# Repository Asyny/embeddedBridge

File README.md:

# embeddedBridge

Develop and test your own embedded system without the need to build a dedicated testbench. It is as easy as following three steps:
1. Connect your device under test to the corresponding GPIOs of the embeddedBridge (see: [Features](#Features))
2. Connect the embeddedBridge to your PC
3. Send commands automatically or manually via the serial connection to the embeddedBridge and thus your device

## Features 

- 4x DOUT (2x 0 - 24 V)
- 4x AOUT (0 - 24 V)
- 4x AIN (max. 27 V)
- 1x FOUT
- 2x Relais (2x SPDT)
- 4x Level shift
- 2x RS232
- 2x CAN
- 1x Battery sim
- ESP8266 interface
- SD card
- EEPROM

## Update

- Download the .uf2 from the newest [release](https://github.com/Asyny/embeddedBridge/releases) assets
- Connect the embeddedBridge via micro USB to your PC
- Press the RESET button and the BOOTSEL simultaneously
- Let go of the RESET and afterwards the BOOTSEL button
- Move the .uf2 into the newly connected USB Drive

## Automatic vs Manual mode

The embeddedBridge will start in the automatic mode where it expects SCPI like commands. If you want to switch to the manual mode where a menu is printed on the serial interface, then you can send the command "SYStem:COMmand:INput MENU". To switch back to the automatic mode, you simple need to exit the menu.

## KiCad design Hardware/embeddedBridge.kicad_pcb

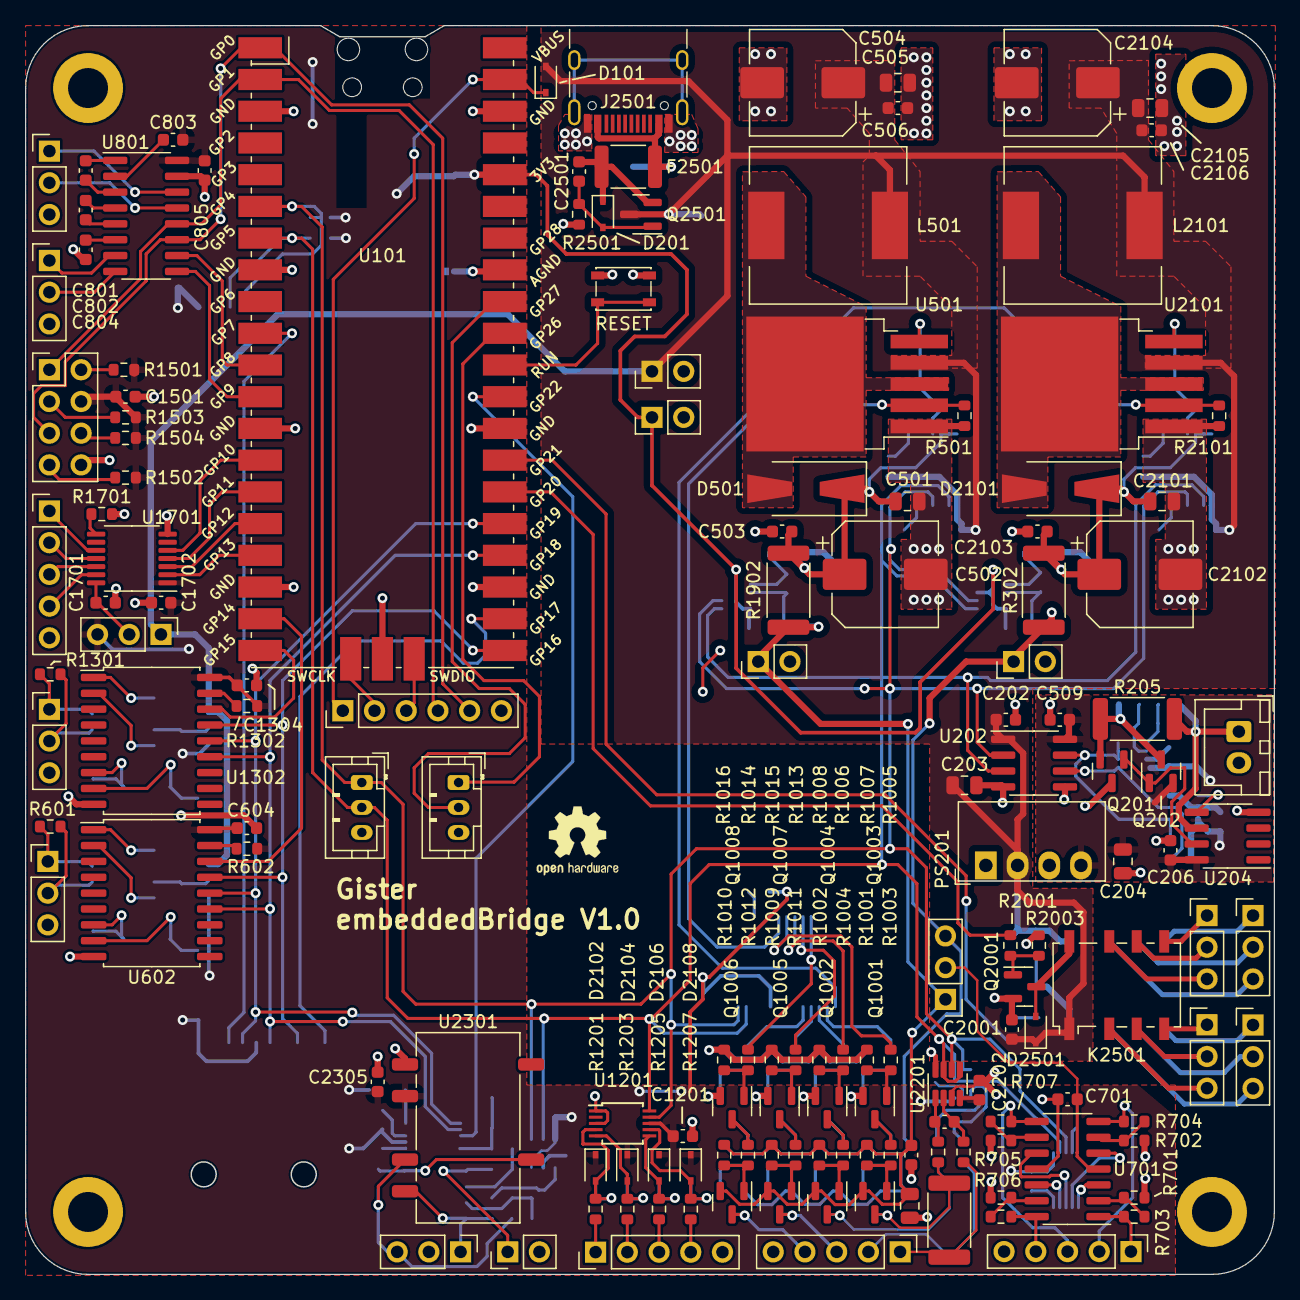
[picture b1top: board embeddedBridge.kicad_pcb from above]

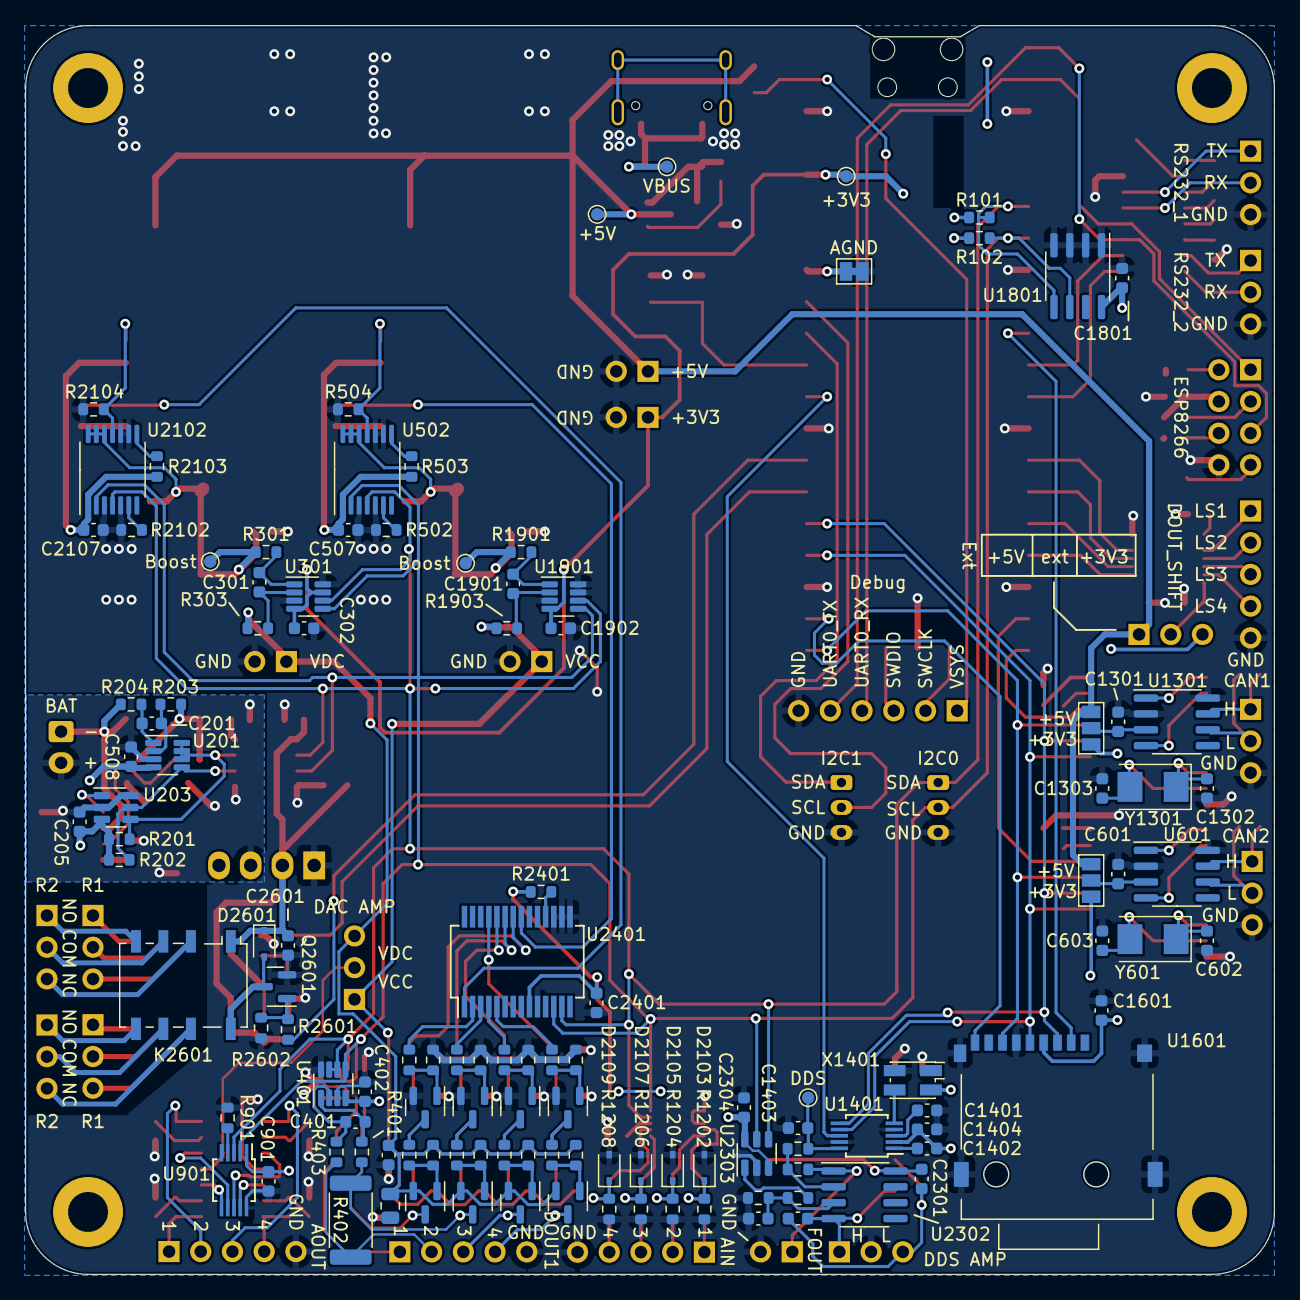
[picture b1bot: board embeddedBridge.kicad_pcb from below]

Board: 2 copper layers, 100.0 x 100.0 mm, 276 parts (122 on the bottom side), 189 nets.

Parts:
C201, C202, C205, C206, C301, C302, C401, C402, C503, C506, C507, C508, C509, C601, C604, C701, C801, C802, C803, C804, C805, C901, C1001, C1101, C1201, C1301, C1304, C1401, C1404, C1501, C1601, C1701, C1702, C1801, C1901, C1902, C2001, C2103, C2106, C2107, C2201, C2202, C2301, C2302, C2304, C2305, C2401, C2501, C2601: 100n; C_0603_1608Metric
C203, C204, C501, C505, C1002, C1102, C2101, C2105: 1u; C_0805_2012Metric
C502, C2102: 220u; CP_Elec_8x10
C504, C2104: 47u; CP_Elec_8x10
C602, C603, C1302, C1303: 22p; C_0603_1608Metric
C1402: 10n; C_0603_1608Metric
C1403: 20p; C_0603_1608Metric
C2303: 680n; C_0603_1608Metric
D101, D201, D2102, D2103, D2104, D2105, D2106, D2107, D2108, D2109, D2501, D2601: 1N5819; D_SOD-323
D501, D2101: D_Schottky; D_SMA-SMB_Universal_Handsoldering
F2501: Polyfuse; Fuse_1812_4532Metric
H101, H102, H103, H104: MountingHole_Pad; MountingHole_3.2mm_M3_DIN965_Pad
J101: AOUT; PinHeader_1x05_P2.54mm_Vertical
J102: I2C1; JST_PH_B3B-PH-K_1x03_P2.00mm_Vertical
J103: I2C0; JST_PH_B3B-PH-K_1x03_P2.00mm_Vertical
J104: Debug; PinHeader_1x06_P2.54mm_Vertical
J105: VCC; PinHeader_1x02_P2.54mm_Vertical
J106: DOUT1; PinHeader_1x05_P2.54mm_Vertical
J107: FOUT; PinHeader_1x02_P2.54mm_Vertical
J108: CAN1; PinHeader_1x03_P2.54mm_Vertical
J109: CAN2; PinHeader_1x03_P2.54mm_Vertical
J110: VDC; PinHeader_1x02_P2.54mm_Vertical
J111: R1_1; PinHeader_1x03_P2.54mm_Vertical
J112: R1_2; PinHeader_1x03_P2.54mm_Vertical
J113: R2_1; PinHeader_1x03_P2.54mm_Vertical
J114: R2_2; PinHeader_1x03_P2.54mm_Vertical
J115: RS232_2; PinHeader_1x03_P2.54mm_Vertical
J116: RS232_1; PinHeader_1x03_P2.54mm_Vertical
J117: +3V3; PinHeader_1x02_P2.54mm_Vertical
J118: +5V; PinHeader_1x02_P2.54mm_Vertical
J201: BAT; JST_XH_B2B-XH-A_1x02_P2.50mm_Vertical
J1201: AIN; PinHeader_1x05_P2.54mm_Vertical
J1501: ESP8266; PinHeader_2x04_P2.54mm_Vertical
J1701: DOUT_SHIFT; PinHeader_1x05_P2.54mm_Vertical
J2501: USB_C_Receptacle_USB2.0; USB_C_Receptacle_HRO_TYPE-C-31-M-12
JP101: AGND; SolderJumper-2_P1.3mm_Bridged_Pad1.0x1.5mm
JP601, JP1301: SolderJumper_3_Open; SolderJumper-3_P1.3mm_Open_Pad1.0x1.5mm_NumberLabels
JP701: DAC AMP; PinHeader_1x03_P2.54mm_Vertical
JP1701: Ext; PinHeader_1x03_P2.54mm_Vertical
JP2301: DDS AMP; PinHeader_1x03_P2.54mm_Vertical
K2501, K2601: G6K-2F-Y; Relay_DPDT_Omron_G6K-2F-Y
L501, L2101: 33uH; L_12x12mm_H8mm
PS201: 1S4E_0505S1U; Converter_DCDC_Murata_MEE1SxxxxSC_THT
Q201: Q_NPN_BCE; SOT-23
Q202: Q_PNP_BCE; SOT-23
Q1001, Q1002, Q1005, Q1006, Q1101, Q1102, Q1105, Q1106, Q2501: Q_PMOS_GSD; SOT-23
Q1003, Q1004, Q1007, Q1008, Q1103, Q1104, Q1107, Q1108: MMBT3904; SOT-23
Q2001, Q2601: Q_NMOS_GSD; SOT-23
R101, R102, R201, R202, R901, R2301: 4k7; R_0603_1608Metric
R203, R204, R301, R303, R401, R403, R1901, R1903, R2201, R2203: 10R; R_0603_1608Metric
R205, R302, R402, R1902, R2202: 100R; R_2512_6332Metric
R501, R502, R503, R602, R701, R702, R705, R706, R1001, R1002, R1005, R1006, R1009, R1010, R1013, R1014, R1101, R1102, R1105, R1106, R1109, R1110, R1113, R1114, R1302, R1501, R1502, R1503, R1504, R1701, R2001, R2101, R2102, R2103, R2304, R2401, R2601: 10k; R_0603_1608Metric
R504, R2104: 470R; R_0603_1608Metric
R601, R1301: 120R; R_0603_1608Metric
R703, R704, R707, R708: 68k; R_0603_1608Metric
R1003, R1004, R1007, R1008, R1011, R1012, R1015, R1016, R1103, R1104, R1107, R1108, R1111, R1112, R1115, R1116, R2003, R2501, R2602: 100k; R_0603_1608Metric
R1201, R1203, R1205, R1207: 12k; R_0603_1608Metric
R1202, R1204, R1206, R1208: 1k5; R_0603_1608Metric
R2302: 39k; R_0603_1608Metric
R2303: 1k; R_0603_1608Metric
SW101: RESET; SW_SPST_PTS810
TP101: +3V3; TestPoint_Pad_D1.0mm
TP102: DDS; TestPoint_Pad_D1.0mm
TP201: VBUS; TestPoint_Pad_D1.0mm
TP202: +5V; TestPoint_Pad_D1.0mm
TP501, TP2101: Boost; TestPoint_Pad_D1.0mm
U101: Pico; RPi_Pico_SMD_TH
U201, U301, U401, U1901, U2201: INA219AxDCN; SOT-23-8
U202: ISO1540; SOIC-8_3.9x4.9mm_P1.27mm
U203, U2303: MCP4725xxx-xCH; SOT-23-6
U204, U2302: Opamp_Dual; SOIC-8_3.9x4.9mm_P1.27mm
U501, U2101: XL6009; TO-263-5_TabPin3
U502, U2102: MCP45HV31-ST; TSSOP-14_4.4x5mm_P0.65mm
U601, U1301: TJA1051T-3; SOIC-8_3.9x4.9mm_P1.27mm
U602, U1302: MCP2515-xSO; SOIC-18W_7.5x11.6mm_P1.27mm
U701: LM324; SOIC-14_3.9x8.7mm_P1.27mm
U801: MAX3232; SOIC-16_3.9x9.9mm_P1.27mm
U901: MCP4728; MSOP-10_3x3mm_P0.5mm
U1201: ADS1115IDGS; TSSOP-10_3x3mm_P0.5mm
U1401: AD9833xRM; MSOP-10_3x3mm_P0.5mm
U1601: TF-01A; FT-01A
U1701: TXB0104PW; TSSOP-14_4.4x5mm_P0.65mm
U1801: 24LC32; SOIC-8_3.9x4.9mm_P1.27mm
U2301: PDS1-M; PSD1
U2401: MCP23017_SS; SSOP-28_5.3x10.2mm_P0.65mm
X1401: XO32; Oscillator_SMD_EuroQuartz_XO32-4Pin_3.2x2.5mm_HandSoldering
Y601, Y1301: 8MHz; Crystal_SMD_5032-2Pin_5.0x3.2mm

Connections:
+3V3: C302.1, C402.1, C604.1, C803.1, C805.1, C901.1, C1201.1, C1304.1, C1402.1, C1404.1, C1501.1, C1601.1, C1702.1, C1801.1, C1902.1, C2202.1, C2304.1, C2305.1, C2401.1, D2102.1 (K), D2104.1 (K), D2106.1 (K), D2108.1 (K), J117.1, J1501.4, JP601.1 (A), JP1301.1 (A), JP1701.3 (B), R101.2, R102.2, R602.1, R1302.1, R1501.1, R1502.1, R1503.2, R1504.2, R2401.1, TP101.1, U101.36 (3V3), U301.4 (VS), U301.7 (A0), U401.4 (VS), U602.18 (VDD), U801.16 (VCC), U901.1 (VDD), U1201.8 (VDD), U1302.18 (VDD), U1401.2 (VDD), U1601.4 (VDD), U1701.1 (VCCA), U1801.8 (VCC), U1901.4 (VS), U2201.4 (VS), U2301.2 (Vin), U2303.3 (VDD), U2303.6 (A0), U2401.9 (VDD), X1401.4 (V+)
+5V: C202.1, C203.1, C504.1, C505.1, C506.1, C507.1, C2001.1, C2104.1, C2105.1, C2106.1, C2107.1, C2601.1, D101.2 (A), D2501.1 (K), D2601.1 (K), J118.1, JP601.3 (B), JP1301.3 (B), JP1701.1 (A), K2501.1, K2601.1, L501.1, L2101.1, PS201.2 (+Vin), Q2501.3 (D), R503.2, R2103.2, TP202.1, U202.1 (VCC1), U501.4 (VIN), U502.1 (VL), U2101.4 (VIN), U2102.1 (VL)
+5VD: C204.1, C205.1, C206.1, C508.1, C509.1, PS201.4 (+Vout), Q201.2 (C), R201.1, R202.1, U201.4 (VS), U202.8 (VCC2), U203.3 (VDD), U204.8 (V+)
/AMP1/IN1+: U701.3 (+), U901.6 (VOUTA)
/AMP1/IN2+: U701.5 (+), U901.7 (VOUTB)
/AMP1/IN3+: U701.10 (+), U901.8 (VOUTC)
/AMP1/IN4+: U701.12 (+), U901.9 (VOUTD)
/AMP1/OUT1: J101.1, R703.2, U701.1
/AMP1/OUT2: J101.2, R704.2, U701.7
/AMP1/OUT3: J101.3, R707.2, U701.8
/AMP1/OUT4: J101.4, R708.2, U701.14
/AMP_offset/IN: C1403.1, R2301.2, TP102.1, U1401.10 (VOUT)
/AMP_offset/OUT: J107.1, R2302.2, U2302.1
/Battery/BAT+: J201.1, R204.1, R205.2, U204.6 (-)
/Battery/BAT+_: Q201.3 (E), Q202.2 (C), R203.1, R205.1
/Battery/SCL_: R202.2, U201.5 (SCL), U202.6 (SCL2), U203.5 (SCL)
/Battery/SDA_: R201.2, U201.6 (SDA), U201.7 (A0), U201.8 (A1), U202.7 (SDA2), U203.4 (SDA)
/CAN1/CANH: J108.1, R1301.2, U1301.7 (CANH)
/CAN1/CANL: J108.2, R1301.1, U1301.6 (CANL)
/CAN2/CANH: J109.1, R601.2, U601.7 (CANH)
/CAN2/CANL: J109.2, R601.1, U601.6 (CANL)
/CD_SD: U101.22 (GPIO17), U1601.9 (CD)
/Cu1+: C501.1, C502.1, C503.1, D501.1 (K), R1901.1, R1902.1, TP501.1, U502.12 (P0W), U502.13 (P0A), U502.14 (V+)
/Cu2+: C2101.1, C2102.1, C2103.1, D2101.1 (K), R301.1, R302.1, TP2101.1, U2102.12 (P0W), U2102.13 (P0A), U2102.14 (V+)
/Cu3+: Q1002.3 (D), Q1102.3 (D), R401.1, R402.1
/Cu3-: J106.2, R402.2, R403.1
/Cu4+: Q1001.3 (D), Q1101.3 (D), R2201.1, R2202.1
/Cu4-: J106.1, R2202.2, R2203.1
/DAC1/LDAC: R901.1, U901.4 (~LDAC)
/DOUT1_LS: U101.14 (GPIO10), U1701.5 (A4)
/DOUT2_LS: U101.15 (GPIO11), U1701.4 (A3)
/DOUT3_LS: U101.16 (GPIO12), U1701.3 (A2)
/DOUT4_LS: U101.17 (GPIO13), U1701.2 (A1)
/ESP8266/EN: J1501.2, R1501.2
/ESP8266/IO0: J1501.6, R1504.1
/ESP8266/IO2: J1501.7, R1502.2
/ESP8266/RST: J1501.3, R1503.1
/I2C0_SCL: J103.2, R102.1, U101.7 (GPIO5), U202.3 (SCL1), U301.5 (SCL), U401.5 (SCL), U502.2 (SCL), U901.2 (SCL), U1201.10 (SCL), U1801.6 (SCL), U1901.5 (SCL), U2102.2 (SCL), U2201.5 (SCL), U2201.7 (A0), U2303.5 (SCL), U2401.12 (SCK)
/I2C0_SDA: J103.1, R101.1, U101.6 (GPIO4), U202.2 (SDA1), U301.6 (SDA), U401.6 (SDA), U401.7 (A0), U502.4 (SDA), U901.3 (SDA), U1201.9 (SDA), U1801.5 (SDA), U1901.6 (SDA), U2102.4 (SDA), U2201.6 (SDA), U2303.4 (SDA), U2401.13 (SDA)
/I2C1_SCL: J102.2, U101.32 (GPIO27_ADC1)
/I2C1_SDA: J102.1, U101.31 (GPIO26_ADC0)
/IO_Expander/GPA1: R1005.1, U2401.22 (GPA1)
/IO_Expander/GPA2: R1006.1, U2401.23 (GPA2)
/IO_Expander/GPA3: R1013.1, U2401.24 (GPA3)
/IO_Expander/GPA4: R1014.1, U2401.25 (GPA4)
/IO_Expander/GPB1: R1105.1, U2401.2 (GPB1)
/IO_Expander/GPB2: R1106.1, U2401.3 (GPB2)
/IO_Expander/GPB3: R1113.1, U2401.4 (GPB3)
/IO_Expander/GPB4: R1114.1, U2401.5 (GPB4)
/Level Shift/OE: R1701.1, U1701.8 (OE)
/Power1/FB: R504.1, U501.5 (FB), U502.11 (P0B)
/Power1/SW: D501.2 (A), L501.2, U501.3 (SW)
/Power2/FB: R2104.1, U2101.5 (FB), U2102.11 (P0B)
/Power2/SW: D2101.2 (A), L2101.2, U2101.3 (SW)
/RUN: SW101.1 (A), U101.30 (RUN)
/Relais1: R2001.1, U101.26 (GPIO20)
/Relais1/COM1: J111.2, K2501.3
/Relais1/COM2: J112.2, K2501.6
/Relais1/NC1: J111.3, K2501.2
/Relais1/NC2: J112.3, K2501.7
/Relais1/NO1: J111.1, K2501.4
/Relais1/NO2: J112.1, K2501.5
/Relais2: R2601.1, U101.27 (GPIO21)
/Relais2/COM1: J113.2, K2601.3
/Relais2/COM2: J114.2, K2601.6
/Relais2/NC1: J113.3, K2601.2
/Relais2/NC2: J114.3, K2601.7
/Relais2/NO1: J113.1, K2601.4
/Relais2/NO2: J114.1, K2601.5
/SPI0_CS_CAN1: U101.20 (GPIO15), U1302.16 (~CS)
/SPI0_CS_CAN2: U101.19 (GPIO14), U602.16 (~CS)
/SPI0_CS_DDS: U101.29 (GPIO22), U1401.8 (~FSYNC)
/SPI0_CS_SD: U101.10 (GPIO7), U1601.2 (CDDAT3(CS))
/SPI0_MISO: U101.21 (GPIO16), U602.15 (SO), U1302.15 (SO), U1601.7 (DAT0(D0))
/SPI0_MOSI: U101.25 (GPIO19), U602.14 (SI), U1302.14 (SI), U1401.6 (SDATA), U1601.3 (CMD(DI))
/SPI0_SCK: U101.24 (GPIO18), U602.13 (SCK), U1302.13 (SCK), U1401.7 (SCLK), U1601.5 (CLK(SCLK))
/SWCLK: J104.2, U101.41 (SWCLK)
/SWDIO: J104.3, U101.43 (SWDIO)
/Switch1/DOUT3: J106.3, Q1005.3 (D), Q1105.3 (D)
/Switch1/DOUT4: J106.4, Q1006.3 (D), Q1106.3 (D)
/UART0_RX: J104.4, J1501.1, U101.2 (GPIO1), U801.12 (R1OUT)
/UART0_TX: J104.5, J1501.5, U101.1 (GPIO0), U801.11 (T1IN)
/UART1_RX: U101.12 (GPIO9), U801.9 (R2OUT)
/UART1_TX: U101.11 (GPIO8), U801.10 (T2IN)
/UART to RS232/RX1: J116.2, U801.13 (R1IN)
/UART to RS232/RX2: J115.2, U801.8 (R2IN)
/UART to RS232/TX1: J116.1, U801.14 (T1OUT)
/UART to RS232/TX2: J115.1, U801.7 (T2OUT)
/USB/VBUS: F2501.1, J2501.A4 (VBUS), J2501.A9 (VBUS), J2501.B4 (VBUS), J2501.B9 (VBUS), TP201.1
/USB/VBUS_FUSED: C2501.1, D201.1 (K), F2501.2, Q2501.2 (S)
/VCC_EN: R501.1, U501.2 (EN), U2401.21 (GPA0)
/VDC_EN: R2101.1, U2101.2 (EN), U2401.1 (GPB0)
/VSYS: D101.1 (K), J104.1, U101.39 (VSYS)
GND: C202.2, C203.2, C302.2, C402.2, C501.2, C502.2, C503.2, C504.2, C505.2, C506.2, C507.2, C601.2, C602.2, C603.2, C604.2, C701.2, C804.1, C805.2, C901.2, C1001.2, C1002.2, C1101.2, C1102.2, C1201.2, C1301.2, C1302.2, C1303.2, C1304.2, C1401.2, C1403.2, C1404.2, C1501.2, C1601.2, C1701.2, C1702.2, C1801.2, C1902.2, C2001.2, C2101.2, C2102.2, C2103.2, C2104.2, C2105.2, C2106.2, C2107.2, C2202.2, C2303.2, C2304.2, C2305.2, C2401.2, C2601.2, D2103.2 (A), D2105.2 (A), D2107.2 (A), D2109.2 (A), J101.5, J102.3, J103.3, J104.6, J105.2, J106.5, J107.2, J108.3, J109.3, J110.2, J115.3, J116.3, J117.2, J118.2, J1201.5, J1501.8, J1701.5, J2501.A1 (GND), J2501.A12 (GND), J2501.B1 (GND), J2501.B12 (GND), JP101.1 (A), JP2301.2 (C), PS201.1 (-Vin), Q1003.2 (E), Q1004.2 (E), Q1007.2 (E), Q1008.2 (E), Q1103.2 (E), Q1104.2 (E), Q1107.2 (E), Q1108.2 (E), Q2001.2 (S), Q2601.2 (S), R501.2, R502.2, R504.2, R701.1, R702.1, R705.1, R706.1, R901.2, R1007.2, R1008.2, R1015.2, R1016.2, R1107.2, R1108.2, R1115.2, R1116.2, R1202.2, R1204.2, R1206.2, R1208.2, R1701.2, R2003.2, R2101.2, R2102.2, R2104.2, R2304.2, R2501.2, R2602.2, SW101.2 (B), U101.3 (GND), U101.8 (GND), U101.13 (GND), U101.18 (GND), U101.23 (GND), U101.28 (GND), U101.38 (GND), U101.42 (GND), U202.4 (GND1), U301.3 (GND), U301.8 (A1), U401.3 (GND), U401.8 (A1), U501.1 (GND), U502.3 (A1), U502.5 (A0), U502.9 (DGND), U502.10 (V-), U601.2 (GND), U601.8 (S), U602.9 (VSS), U701.11 (V-), U801.15 (GND), U901.10 (VSS), U1201.1 (ADDR), U1201.3 (GND), U1301.2 (GND), U1301.8 (S), U1302.9 (VSS), U1401.4 (DGND), U1401.9 (AGND), U1601.6 (VSS), U1601.10 (GND), U1601.11 (GND), U1601.12 (GND), U1601.13 (GND), U1701.7 (GND), U1801.1 (A0), U1801.2 (A1), U1801.3 (A2), U1801.4 (GND), U1901.3 (GND), U1901.7 (A0), U1901.8 (A1), U2101.1 (GND), U2102.3 (A1), U2102.5 (A0), U2102.9 (DGND), U2102.10 (V-), U2201.3 (GND), U2201.8 (A1), U2301.1 (GND), U2303.2 (VSS), U2401.10 (VSS), U2401.15 (A0), U2401.16 (A1), U2401.17 (A2), X1401.2 (GND)
GNDA: JP101.2 (B), U101.33 (AGND)
GNDD: C204.2, C205.2, C206.2, C508.2, C509.2, J201.2, PS201.3 (-Vout), Q202.3 (E), U201.3 (GND), U202.5 (GND2), U203.2 (VSS), U203.6 (A0), U204.4 (V-)
unnamed: C201.1, R203.2, U201.2 (IN-)
unnamed: C201.2, R204.2, U201.1 (IN+)
unnamed: C301.1, R301.2, U301.1 (IN+)
unnamed: C301.2, R303.2, U301.2 (IN-)
unnamed: C401.1, R401.2, U401.1 (IN+)
unnamed: C401.2, R403.2, U401.2 (IN-)
unnamed: C601.1, JP601.2 (C), U601.3 (VCC)
unnamed: C602.1, U602.7 (OSC2), Y601.1
unnamed: C603.1, U602.8 (OSC1), Y601.2
unnamed: C701.1, JP701.2 (C), U701.4 (V+)
unnamed: C801.1, U801.3 (C1-)
unnamed: C801.2, U801.1 (C1+)
unnamed: C802.1, U801.5 (C2-)
unnamed: C802.2, U801.4 (C2+)
unnamed: C803.2, U801.2 (VS+)
unnamed: C804.2, U801.6 (VS-)
unnamed: C1301.1, JP1301.2 (C), U1301.3 (VCC)
unnamed: C1302.1, U1302.7 (OSC2), Y1301.1
unnamed: C1303.1, U1302.8 (OSC1), Y1301.2
unnamed: C1401.1, U1401.3 (CAP/2.5V)
unnamed: C1402.2, U1401.1 (COMP)
unnamed: C1701.1, JP1701.2 (C), U1701.14 (VCCB)
unnamed: C1901.1, R1901.2, U1901.1 (IN+)
unnamed: C1901.2, R1903.2, U1901.2 (IN-)
unnamed: C2201.1, R2201.2, U2201.1 (IN+)
unnamed: C2201.2, R2203.2, U2201.2 (IN-)
unnamed: C2301.1, U2301.7 (+Vo), U2302.8 (V+)
unnamed: C2301.2, C2302.1, JP2301.3 (B), U2301.4 (0V)
unnamed: C2302.2, JP2301.1 (A), U2301.5 (-Vo), U2302.4 (V-)
unnamed: C2303.1, R2303.1, R2304.1, U2302.3 (+)
unnamed: C2501.2, D201.2 (A), Q2501.1 (G), R2501.1
unnamed: D2102.2 (A), D2103.1 (K), R1201.2, R1202.1, U1201.4 (AIN0)
unnamed: D2104.2 (A), D2105.1 (K), R1203.2, R1204.1, U1201.5 (AIN1)
unnamed: D2106.2 (A), D2107.1 (K), R1205.2, R1206.1, U1201.6 (AIN2)
unnamed: D2108.2 (A), D2109.1 (K), R1207.2, R1208.1, U1201.7 (AIN3)
unnamed: D2501.2 (A), K2501.8, Q2001.3 (D)
unnamed: D2601.2 (A), K2601.8, Q2601.3 (D)
unnamed: J1201.1, R1201.1
unnamed: J1201.2, R1203.1
unnamed: J1201.3, R1205.1
unnamed: J1201.4, R1207.1
unnamed: J1701.1, U1701.10 (B4)
unnamed: J1701.2, U1701.11 (B3)
unnamed: J1701.3, U1701.12 (B2)
unnamed: J1701.4, U1701.13 (B1)
unnamed: Q201.1 (B), Q202.1 (B), U204.7
unnamed: Q1001.1 (G), R1001.2, R1003.1
unnamed: Q1002.1 (G), R1002.2, R1004.1
unnamed: Q1003.1 (B), R1005.2, R1007.1
unnamed: Q1003.3 (C), R1003.2
unnamed: Q1004.1 (B), R1006.2, R1008.1
unnamed: Q1004.3 (C), R1004.2
unnamed: Q1005.1 (G), R1009.2, R1011.1
unnamed: Q1006.1 (G), R1010.2, R1012.1
unnamed: Q1007.1 (B), R1013.2, R1015.1
unnamed: Q1007.3 (C), R1011.2
unnamed: Q1008.1 (B), R1014.2, R1016.1
unnamed: Q1008.3 (C), R1012.2
unnamed: Q1101.1 (G), R1101.2, R1103.1
unnamed: Q1102.1 (G), R1102.2, R1104.1
unnamed: Q1103.1 (B), R1105.2, R1107.1
unnamed: Q1103.3 (C), R1103.2
unnamed: Q1104.1 (B), R1106.2, R1108.1
unnamed: Q1104.3 (C), R1104.2
unnamed: Q1105.1 (G), R1109.2, R1111.1
unnamed: Q1106.1 (G), R1110.2, R1112.1
unnamed: Q1107.1 (B), R1113.2, R1115.1
unnamed: Q1107.3 (C), R1111.2
unnamed: Q1108.1 (B), R1114.2, R1116.1
unnamed: Q1108.3 (C), R1112.2
unnamed: Q2001.1 (G), R2001.2, R2003.1
unnamed: Q2601.1 (G), R2601.2, R2602.1
unnamed: R502.1, U502.6 (~WLAT)
unnamed: R503.1, U502.8 (~SHDN)
unnamed: R602.2, U602.17 (~RESET)
unnamed: R701.2, R703.1, U701.2 (-)
unnamed: R702.2, R704.1, U701.6 (-)
unnamed: R705.2, R707.1, U701.9 (-)
unnamed: R706.2, R708.1, U701.13 (-)
unnamed: R1302.2, U1302.17 (~RESET)
unnamed: R2102.1, U2102.6 (~WLAT)
unnamed: R2103.1, U2102.8 (~SHDN)
unnamed: R2301.1, R2302.1, U2302.2 (-)
unnamed: R2303.2, U2303.1 (VOUT)
unnamed: R2401.2, U2401.18 (~RESET)
unnamed: U203.1 (VOUT), U204.5 (+)
unnamed: U601.1 (TXD), U602.1 (TXCAN)
unnamed: U601.4 (RXD), U602.2 (RXCAN)
unnamed: U1301.1 (TXD), U1302.1 (TXCAN)
unnamed: U1301.4 (RXD), U1302.2 (RXCAN)
unnamed: U1401.5 (MCLK), X1401.3 (OUT)
VCC: C1001.1, C1002.1, J105.1, JP701.1 (A), Q1001.2 (S), Q1002.2 (S), Q1005.2 (S), Q1006.2 (S), R1001.1, R1002.1, R1009.1, R1010.1, R1902.2, R1903.1
VDC: C1101.1, C1102.1, J110.1, JP701.3 (B), Q1101.2 (S), Q1102.2 (S), Q1105.2 (S), Q1106.2 (S), R302.2, R303.1, R1101.1, R1102.1, R1109.1, R1110.1

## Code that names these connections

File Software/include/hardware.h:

#ifndef HARDWARE_H
#define HARDWARE_H

// third party libraries
#include <Arduino.h>
#include <Arduino_DebugUtils.h>

#define DEBUG_SERIAL Serial1
#define DEBUG_LEVEL DBG_WARNING	// DBG_NONE, DBG_ERROR, DBG_WARNING, DBG_INFO, DBG_DEBUG, DBG_VERBOSE

// datasheets
//MCP45HV31 https://eu.mouser.com/datasheet/2/268/20005304A-347268.pdf

// Serial
#define SERIAL_BAUD 115200
// UART
#define UART0_BAUD 115200
#define UART0_TX 0
#define UART0_RX 1
#define UART1_BAUD 115200
#define UART1_TX 8
#define UART1_RX 9

// SPI
#define SPI0_SCK 18
#define SPI0_MOSI 19
#define SPI0_MISO 16
// SPI CS
#define AD9833_DDS_CS 22
#define MCP2515_CAN1_CS 15
#define MCP2515_CAN2_CS 14
#define SD_CS 7

// GPIOs
#define LED_PIN 25
#define RELAIS1_PIN 20
#define RELAIS2_PIN 21
#define LEVELSHIFT1_PIN 10
#define LEVELSHIFT2_PIN 11
#define LEVELSHIFT3_PIN 12
#define LEVELSHIFT4_PIN 13
#define AMP_HL 3
#define SD_CD 17

// I2C
#define I2C0_SDA 4
#define I2C0_SCL 5
#define I2C1_SDA 26
#define I2C1_SCL 27
// I2C Adresses
#define INA219_VCC_ADDR 0x40
#define INA219_VDC_ADDR 0x41
#define INA219_DOUT1_ADDR 0x42
#define INA219_DOUT2_ADDR 0x43
#define INA219_BAT_ADDR 0x4A
#define MCP23017_DOUT_ADDR 0x20	
//#define MCP4728_AOUT_ADDR 0x60	// ToDo: BUG same adress as MCP4725 Battery
#define MCP4725_BAT_ADDR 0x60 // AJxx=110000n, APxx=110001n, AQxx=110010n, ARxx=110011n
#define MCP4725_DDSOFFSET_ADDR 0x61
#define ADS1115_AIN_ADDR 0x48
#define EEPROM_ADDR 0x50
#define MCP45HV31_VCC_ADDR 0x3C
#define MCP45HV31_VDC_ADDR 0x3D	// ToDo: BUG same address as MCP45HV31_VCC_ADDR

// MCP23017 GPIOs
#define VCC_EN_PIN 0
#define VCC_DOUT1_PIN 1
#define VCC_DOUT2_PIN 2
#define VCC_DOUT3_PIN 3
#define VCC_DOUT4_PIN 4
//#define UNUSED 5
//#define UNUSED 6
//#define UNUSED 7
#define VDC_EN_PIN 8
#define VDC_DOUT1_PIN 9
#define VDC_DOUT2_PIN 10
#define VDC_DOUT3_PIN 11
#define VDC_DOUT4_PIN 12
//#define UNUSED 13
//#define UNUSED 14
//#define UNUSED 15

// Settings
#define VCC_VDC_MAX_VOLTAGE 27.0

#define MCP23017_MAX_PIN 15

#define AIN1_VOLTAGE_DEVIDER 9.1266
#define AIN2_VOLTAGE_DEVIDER 9.1266
#define AIN3_VOLTAGE_DEVIDER 9.1266
#define AIN4_VOLTAGE_DEVIDER 9.1266

#define FOUT_OFFSET_MULTIPLIER 160
#define BAT_MULTIPLIER 790
#define VCC_VOLTAGE_MULTIPLIER 4.561 // 1.25*(1+100k/4k7)=27.846V; max wiper (100k) = 127 -> 27.846 = 127, 0.219 = 1
#define VDC_VOLTAGE_MULTIPLIER 4.561

#define MENU_SERIAL Serial

#endif // HARDWARE_H

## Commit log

2022-07-14 layout
2022-07-14 added readme
2022-08-29 add software
2022-12-05 introduce HAL
2022-12-06 move serial menu to separate file (partly working)
2022-12-07 move serial menu to separate file (working)
2022-12-12 set USB port as menu serial; fix AIN2_VOLTAGE_DEVIDER values
2022-12-12 introduce data model for setting and getting hardware (global variables with namespace)
2022-12-12 move all menu serial variables into global scope
2022-12-12 set debug build option as default
2022-12-12 move functions for reading hardware into separate class
2022-12-12 add support for reading INA219 values
2022-12-19 remove Vrekrer SCPI parser library
2022-12-19 switch to debug serial interface
2022-12-19 add support to switch between SCPI and MENU SERIAL interface for sending commands
2022-12-19 add buffered reading from serial interface
2022-12-19 introduce debug level
2022-12-19 centralize HAL access via DataHandling component, remove HAL dependency from CommandHandling
2022-12-19 fix compiler warnings
2022-12-20 set initial ADC gain to 1 instead of auto (auto is not supported)
2022-12-20 add SCPI command handling for ADC, relais, and level shift
2022-12-20 add further SCPi commands
2022-12-20 add scpi commands for digital output
2022-12-21 increase performance of SCPI commands
2022-12-21 fix EOL handling for SCPI commands
2022-12-22 add error response to SCPI commads; minor improvements for serial
2022-12-22 add demo client for testing
2023-01-09 support windows and linux termination characters for serial input
2023-01-09 add documentation of supported SCPI commands
2023-01-20 add licenses
2023-01-20 move client demo
2023-01-20 move platformio ini
2023-01-20 simple description
2023-01-20 moved commands to wiki
2023-01-21 added pictures
